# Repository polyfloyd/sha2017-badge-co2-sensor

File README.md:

SHA2017 Badge CO2 Sensor
========================

**NOTE: This app has been replaced by esphome and is thus unmaintained**

MicroPython program for reading an MH-Z19 carbon dioxide sensor. The values are
displayed on the badge's display as a single stat and graph, pushed to MQTT and
used as a trigger for alerts.

Also reads a BME280 climate sensor as a bonus.

The CO2 warning thresholds are set to levels suitable to reduce the risk of
Coronavirus infections.

The MQTT topics are listed below, the value is the raw decimal number without
unit. The prefix and (room) name can be altered by setting them with the
`machine.nvs_setstr` functions over a serial connection.

* `${mqtt.prefix}/${name}/co2_ppm`
* `${mqtt.prefix}/${name}/temperature_c`
* `${mqtt.prefix}/${name}/pressure_hpa`
* `${mqtt.prefix}/${name}/humidity_pct`

NVS settings:

| Space     | Key           | Default                   |
|-----------|---------------|---------------------------|
| `owner`   | `name`        | `<whatever you have set>` |
| `sensors` | `mqtt.server` | `test.mosquitto.org`      |
| `sensors` | `mqtt.prefix` | `space/climate`           |

This app is published on the SHA Badge repository, install
`sha2017_badge_co2_sensor` to get it. You may also want to set the NVS setting
`system`/`default_app` to launch it on powerup.

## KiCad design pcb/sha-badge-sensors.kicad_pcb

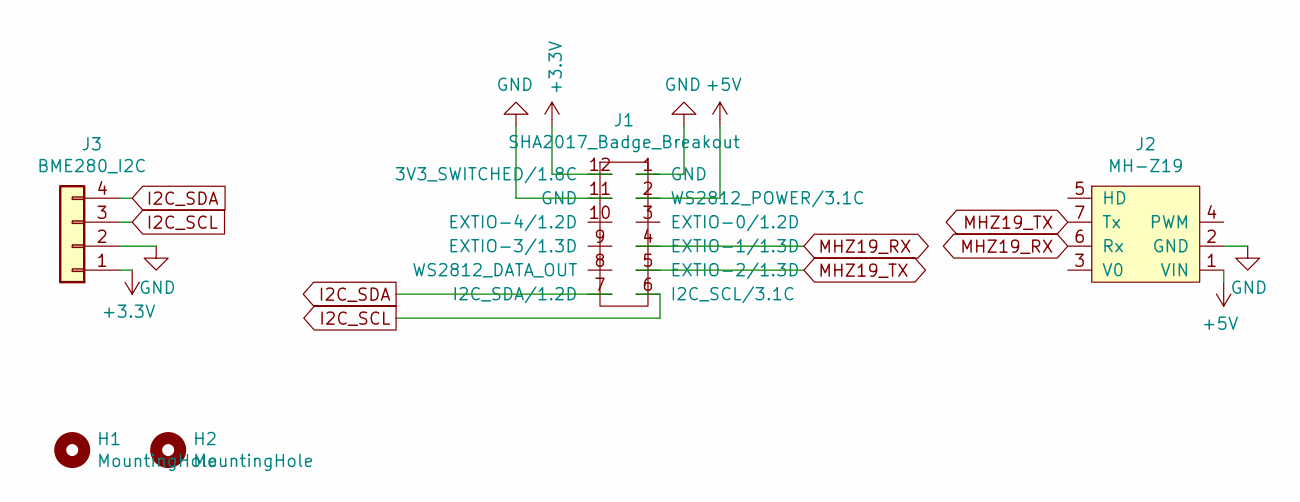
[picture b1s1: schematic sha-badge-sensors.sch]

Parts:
H1, H2: MountingHole; MountingHole_4mm
J1: SHA2017_Badge_Breakout
J2: MH-Z19; Sensor_MH-Z19
J3: BME280_I2C; PinHeader_1x04_P2.54mm_Vertical

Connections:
+3V3: J1.12 (3V3_SWITCHED/1.8C), J3.1
+5V: J1.2 (WS2812_POWER/3.1C), J2.1 (VIN)
GND: J1.1 (GND), J1.11 (GND), J2.2 (GND), J3.2
I2C_SCL: J1.6 (I2C_SCL/3.1C), J3.3
I2C_SDA: J1.7 (I2C_SDA/1.2D), J3.4
MHZ19_RX: J1.4 (EXTIO-1/1.3D), J2.6 (Rx)
MHZ19_TX: J1.5 (EXTIO-2/1.3D), J2.7 (Tx)

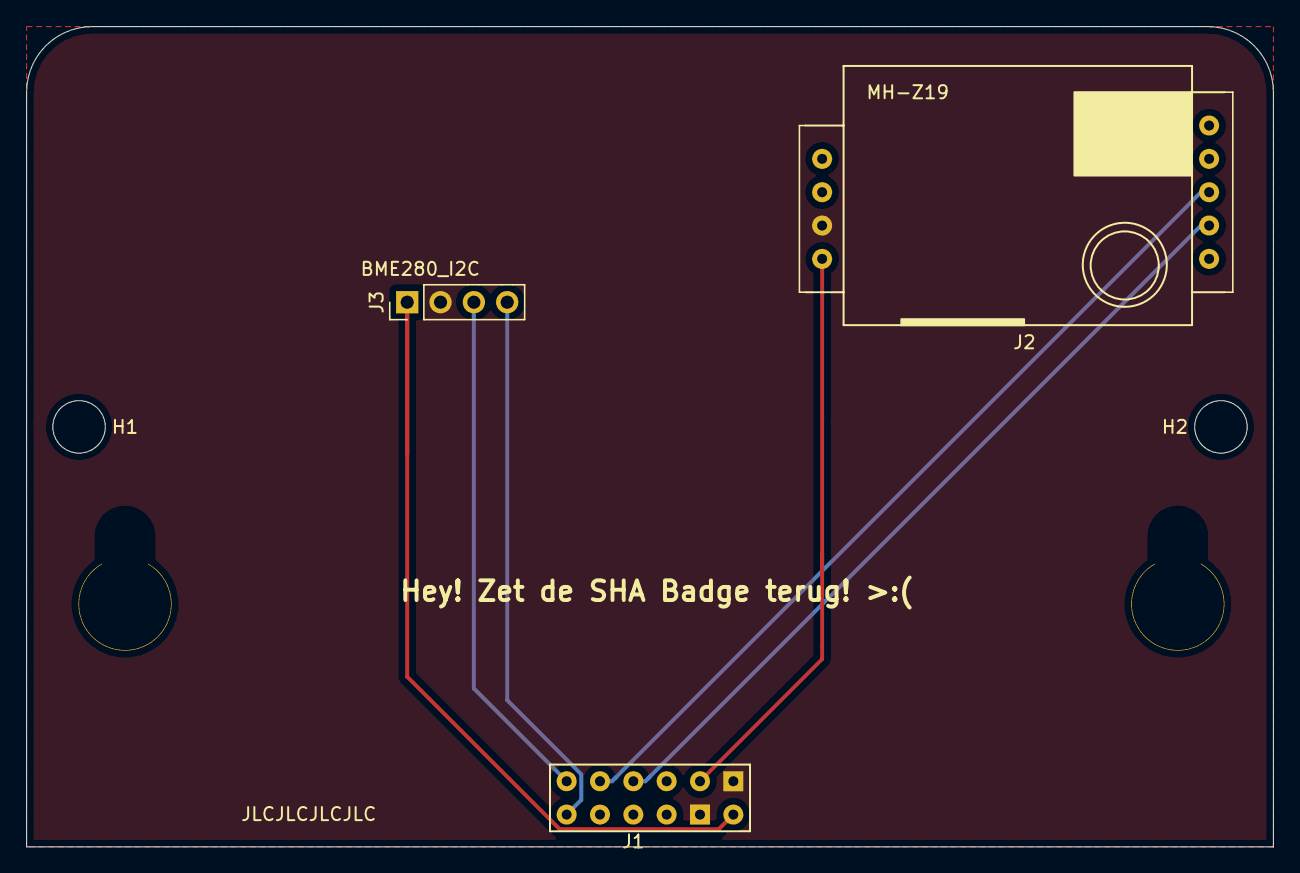
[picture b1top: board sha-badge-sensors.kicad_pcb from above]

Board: 2 copper layers, 95.0 x 62.5 mm, 5 parts (0 on the bottom side), 7 nets.

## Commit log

2020-12-04 Add MH-Z19b Python driver
2020-12-04 Add initial value display and graph
2020-12-12 Add labels for the Y axis
2021-01-14 Add labels for the X axis
2021-01-14 Update pin header description
2021-01-14 Add KiCAD PCB files
2021-01-14 Prevent hammering the E-Ink display by caching rendered values
2021-01-14 Fix graph Y axis orientation
2021-01-14 Implement reading the BME280 sensor
2021-01-17 Fall back to displaying relative time offsets if NTP is not synced
2021-01-17 Attempt to synchronize with the NTP server
2021-01-17 Add CO2 threshold warning messages
2021-01-17 Use LEDs for warnings
2021-01-17 Export sensor readings over MQTT
2021-01-18 Add readme
2021-01-18 Fix nvs_getstr import
2021-01-18 Add installation instructions to readme
2021-01-29 Add a photo of the assembled module
2021-02-12 WIP: Debug mock
2024-04-06 Deprecation notice
